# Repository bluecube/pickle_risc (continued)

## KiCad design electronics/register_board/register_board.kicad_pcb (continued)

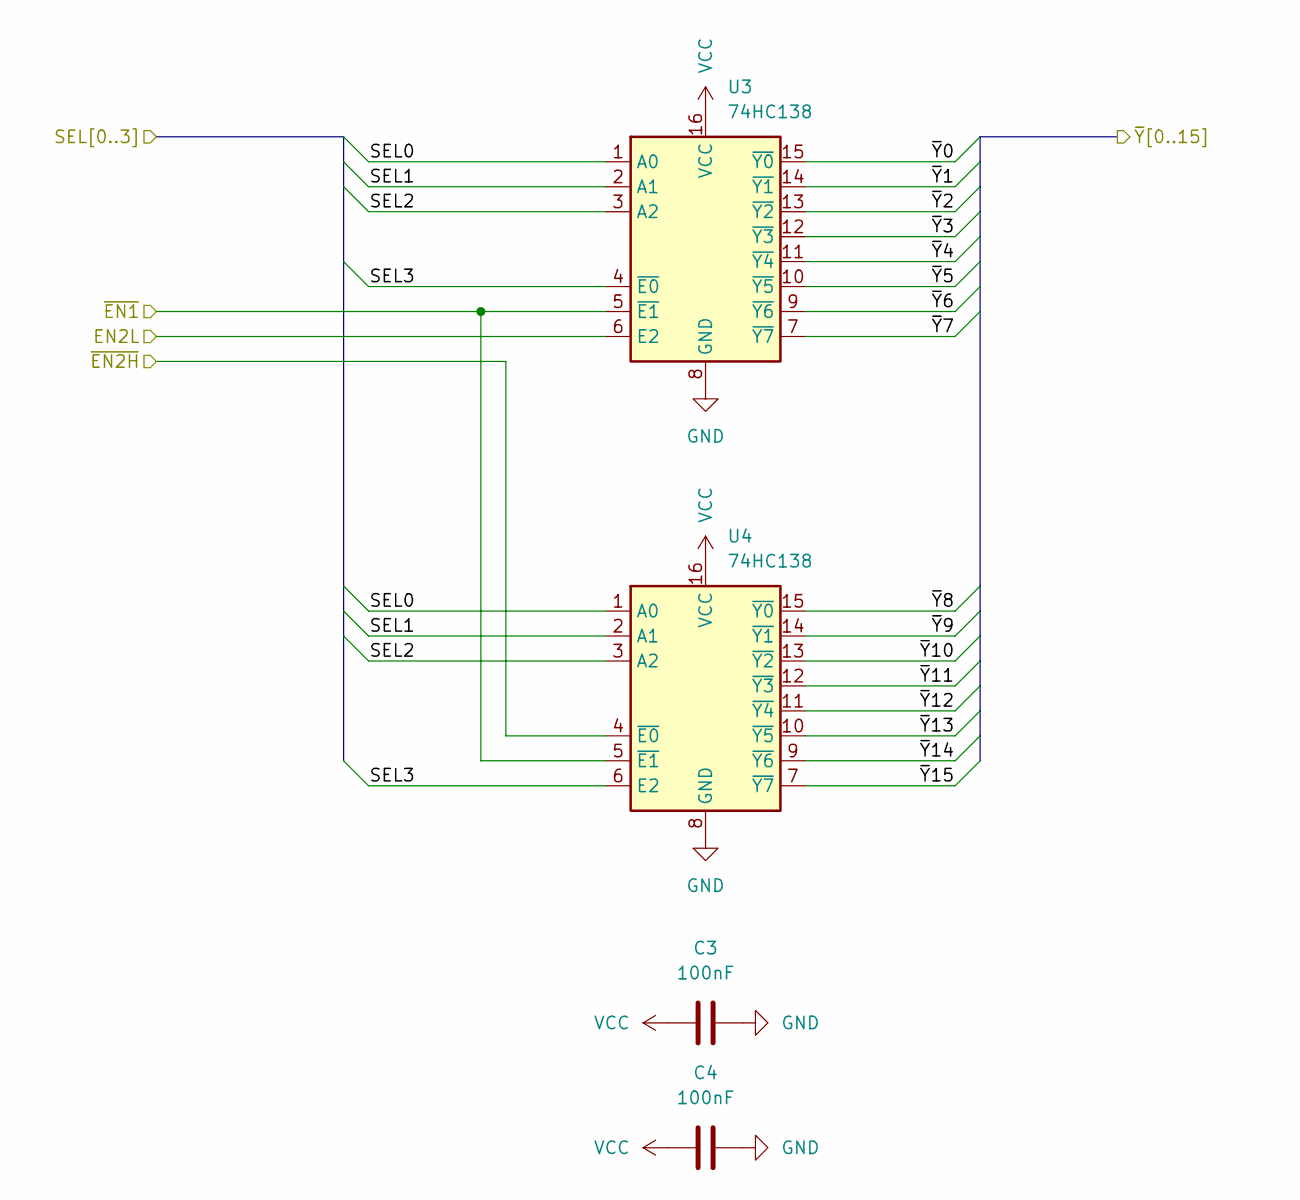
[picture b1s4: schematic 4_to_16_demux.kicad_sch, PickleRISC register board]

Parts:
C3, C4: 100nF; C_0603_1608Metric
U3, U4: 74HC138; TSSOP-16_L5.0-W4.4-P0.65-LS6.4-BL

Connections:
/decoding/4 to 16 demux1/SEL0: U3.1 (A0), U4.1 (A0)
/decoding/4 to 16 demux1/SEL1: U3.2 (A1), U4.2 (A1)
/decoding/4 to 16 demux1/SEL2: U3.3 (A2), U4.3 (A2)
/decoding/4 to 16 demux1/SEL3: U3.4 (~E0), U4.6 (E2)
/decoding/~A_EN: U3.5 (~E1), U4.5 (~E1); also elsewhere on the board
/decoding/~A_EN0: U3.15 (~Y0); also elsewhere on the board
/decoding/~A_EN1: U3.14 (~Y1); also elsewhere on the board
/decoding/~A_EN2: U3.13 (~Y2); also elsewhere on the board
/decoding/~A_EN3: U3.12 (~Y3); also elsewhere on the board
/decoding/~A_EN4: U3.11 (~Y4); also elsewhere on the board
/decoding/~A_EN5: U3.10 (~Y5); also elsewhere on the board
/decoding/~A_EN6: U3.9 (~Y6); also elsewhere on the board
/decoding/~A_EN7: U3.7 (~Y7); also elsewhere on the board
/decoding/~A_EN8: U4.15 (~Y0); also elsewhere on the board
/decoding/~A_EN9: U4.14 (~Y1); also elsewhere on the board
/decoding/~A_EN10: U4.13 (~Y2); also elsewhere on the board
/decoding/~A_EN11: U4.12 (~Y3); also elsewhere on the board
/decoding/~A_EN12: U4.11 (~Y4); also elsewhere on the board
/decoding/~A_EN13: U4.10 (~Y5); also elsewhere on the board
/decoding/~A_EN14: U4.9 (~Y6); also elsewhere on the board
/decoding/~A_EN15: U4.7 (~Y7); also elsewhere on the board
GND: C3.2, C4.2, U3.8 (GND), U4.4 (~E0), U4.8 (GND); also elsewhere on the board
VCC: C3.1, C4.1, U3.6 (E2), U3.16 (VCC), U4.16 (VCC); also elsewhere on the board

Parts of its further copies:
C5, C6, C7, C8: 100nF; C_0603_1608Metric
U5, U6, U7, U8: 74HC138; TSSOP-16_L5.0-W4.4-P0.65-LS6.4-BL

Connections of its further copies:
/B_SEL0: U5.1 (A0), U6.1 (A0)
/B_SEL1: U5.2 (A1), U6.2 (A1)
/B_SEL2: U5.3 (A2), U6.3 (A2)
/B_SEL3: U5.4 (~E0), U6.6 (E2)
/CLK: U7.5 (~E1), U8.5 (~E1); also elsewhere on the board
/D_SEL_LATCHED0: U7.1 (A0), U8.1 (A0); also elsewhere on the board
/D_SEL_LATCHED1: U7.2 (A1), U8.2 (A1); also elsewhere on the board
/D_SEL_LATCHED2: U7.3 (A2), U8.3 (A2); also elsewhere on the board
/D_SEL_LATCHED3: U7.4 (~E0), U8.6 (E2); also elsewhere on the board
/LOAD_LATCHED: U7.6 (E2); also elsewhere on the board
/decoding/4 to 16 demux3/~EN2H: U8.4 (~E0); also elsewhere on the board
/decoding/CLK0: U7.15 (~Y0)
/decoding/CLK1: U7.14 (~Y1); also elsewhere on the board
/decoding/CLK2: U7.13 (~Y2); also elsewhere on the board
/decoding/CLK3: U7.12 (~Y3); also elsewhere on the board
/decoding/CLK4: U7.11 (~Y4); also elsewhere on the board
/decoding/CLK5: U7.10 (~Y5); also elsewhere on the board
/decoding/CLK6: U7.9 (~Y6); also elsewhere on the board
/decoding/CLK7: U7.7 (~Y7); also elsewhere on the board
/decoding/CLK8: U8.15 (~Y0); also elsewhere on the board
/decoding/CLK9: U8.14 (~Y1); also elsewhere on the board
/decoding/CLK10: U8.13 (~Y2); also elsewhere on the board
/decoding/CLK11: U8.12 (~Y3); also elsewhere on the board
/decoding/CLK12: U8.11 (~Y4); also elsewhere on the board
/decoding/CLK13: U8.10 (~Y5); also elsewhere on the board
/decoding/CLK14: U8.9 (~Y6); also elsewhere on the board
/decoding/CLK15: U8.7 (~Y7); also elsewhere on the board
/decoding/~B_EN0: U5.15 (~Y0); also elsewhere on the board
/decoding/~B_EN1: U5.14 (~Y1); also elsewhere on the board
/decoding/~B_EN2: U5.13 (~Y2); also elsewhere on the board
/decoding/~B_EN3: U5.12 (~Y3); also elsewhere on the board
/decoding/~B_EN4: U5.11 (~Y4); also elsewhere on the board
/decoding/~B_EN5: U5.10 (~Y5); also elsewhere on the board
/decoding/~B_EN6: U5.9 (~Y6); also elsewhere on the board
/decoding/~B_EN7: U5.7 (~Y7); also elsewhere on the board
/decoding/~B_EN8: U6.15 (~Y0); also elsewhere on the board
/decoding/~B_EN9: U6.14 (~Y1); also elsewhere on the board
/decoding/~B_EN10: U6.13 (~Y2); also elsewhere on the board
/decoding/~B_EN11: U6.12 (~Y3); also elsewhere on the board
/decoding/~B_EN12: U6.11 (~Y4); also elsewhere on the board
/decoding/~B_EN13: U6.10 (~Y5); also elsewhere on the board
/decoding/~B_EN14: U6.9 (~Y6); also elsewhere on the board
/decoding/~B_EN15: U6.7 (~Y7); also elsewhere on the board
/~B_EN: U5.5 (~E1), U6.5 (~E1)
GND: C5.2, C6.2, C7.2, C8.2, U5.8 (GND), U6.4 (~E0), U6.8 (GND), U7.8 (GND), U8.8 (GND); also elsewhere on the board
VCC: C5.1, C6.1, C7.1, C8.1, U5.6 (E2), U5.16 (VCC), U6.16 (VCC), U7.16 (VCC), U8.16 (VCC); also elsewhere on the board

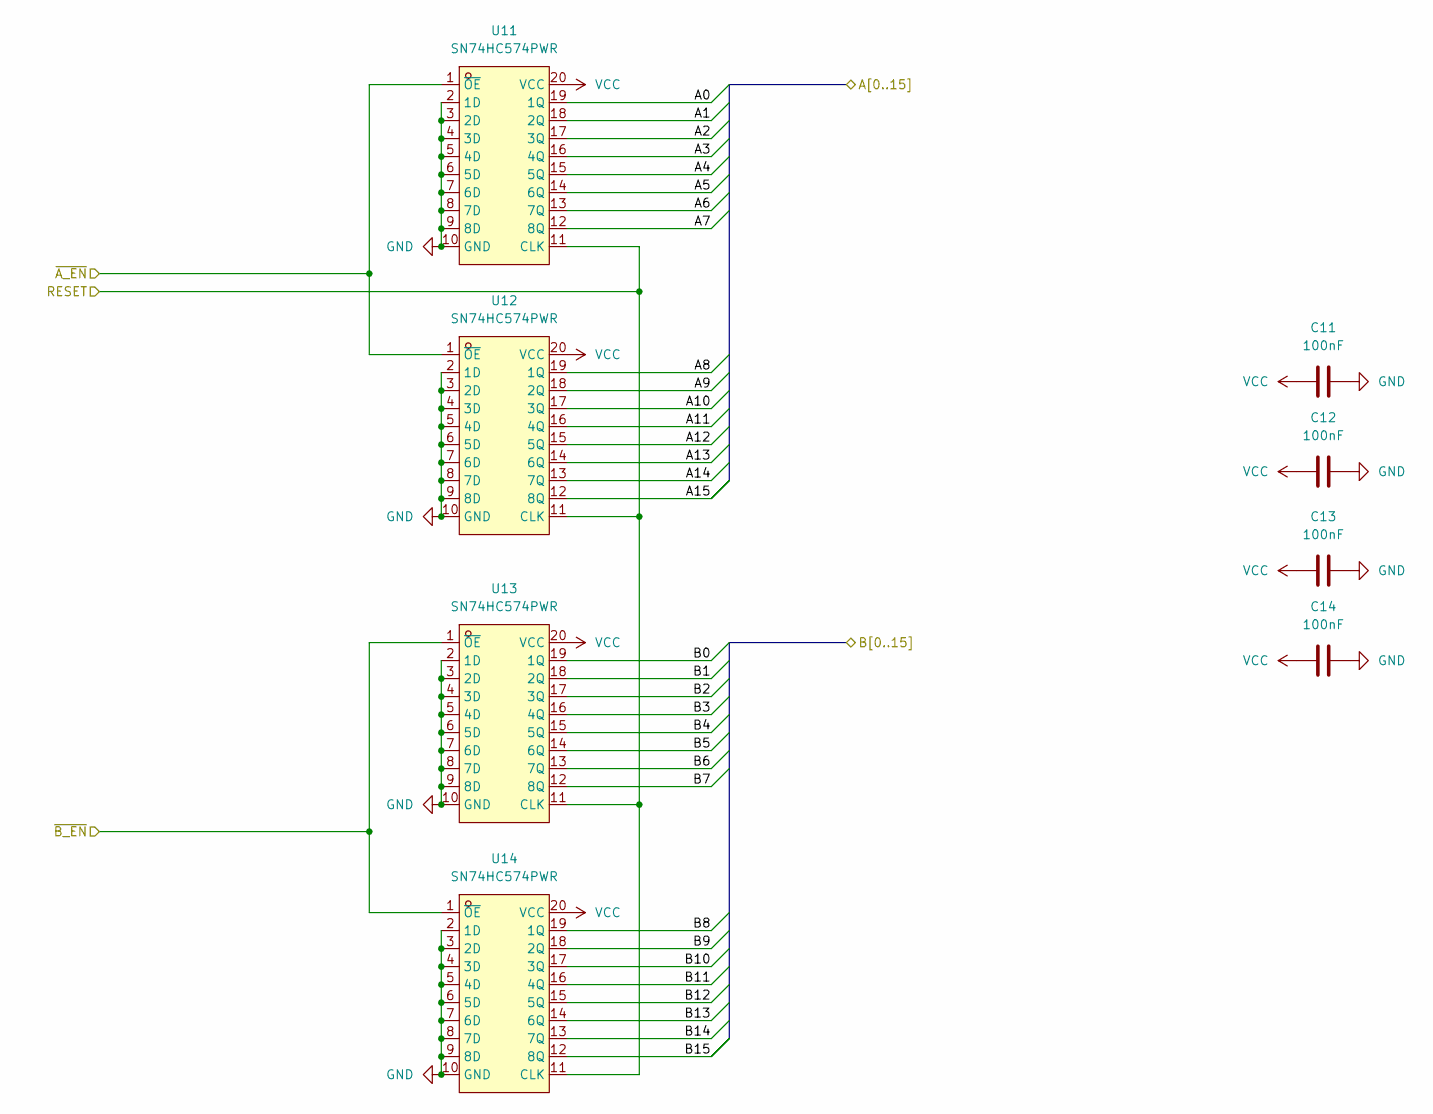
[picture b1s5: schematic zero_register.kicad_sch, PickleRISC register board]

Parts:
C11, C12, C13, C14: 100nF; C_0603_1608Metric
U11, U12, U13, U14: SN74HC574PWR; TSSOP-20_L6.5-W4.4-P0.65-LS6.4-BL; LCSC Part C132111

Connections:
/A0: U11.19 (1Q); also elsewhere on the board
/A1: U11.18 (2Q); also elsewhere on the board
/A2: U11.17 (3Q); also elsewhere on the board
/A3: U11.16 (4Q); also elsewhere on the board
/A4: U11.15 (5Q); also elsewhere on the board
/A5: U11.14 (6Q); also elsewhere on the board
/A6: U11.13 (7Q); also elsewhere on the board
/A7: U11.12 (8Q); also elsewhere on the board
/A8: U12.19 (1Q); also elsewhere on the board
/A9: U12.18 (2Q); also elsewhere on the board
/A10: U12.17 (3Q); also elsewhere on the board
/A11: U12.16 (4Q); also elsewhere on the board
/A12: U12.15 (5Q); also elsewhere on the board
/A13: U12.14 (6Q); also elsewhere on the board
/A14: U12.13 (7Q); also elsewhere on the board
/A15: U12.12 (8Q); also elsewhere on the board
/B0: U13.19 (1Q); also elsewhere on the board
/B1: U13.18 (2Q); also elsewhere on the board
/B2: U13.17 (3Q); also elsewhere on the board
/B3: U13.16 (4Q); also elsewhere on the board
/B4: U13.15 (5Q); also elsewhere on the board
/B5: U13.14 (6Q); also elsewhere on the board
/B6: U13.13 (7Q); also elsewhere on the board
/B7: U13.12 (8Q); also elsewhere on the board
/B8: U14.19 (1Q); also elsewhere on the board
/B9: U14.18 (2Q); also elsewhere on the board
/B10: U14.17 (3Q); also elsewhere on the board
/B11: U14.16 (4Q); also elsewhere on the board
/B12: U14.15 (5Q); also elsewhere on the board
/B13: U14.14 (6Q); also elsewhere on the board
/B14: U14.13 (7Q); also elsewhere on the board
/B15: U14.12 (8Q); also elsewhere on the board
/RESET: U11.11 (CLK), U12.11 (CLK), U13.11 (CLK), U14.11 (CLK)
/decoding/~A_EN0: U11.1 (~OE), U12.1 (~OE); also elsewhere on the board
/decoding/~B_EN0: U13.1 (~OE), U14.1 (~OE); also elsewhere on the board
GND: C11.2, C12.2, C13.2, C14.2, U11.2 (1D), U11.3 (2D), U11.4 (3D), U11.5 (4D), U11.6 (5D), U11.7 (6D), U11.8 (7D), U11.9 (8D), U11.10 (GND), U12.2 (1D), U12.3 (2D), U12.4 (3D), U12.5 (4D), U12.6 (5D), U12.7 (6D), U12.8 (7D), U12.9 (8D), U12.10 (GND), U13.2 (1D), U13.3 (2D), U13.4 (3D), U13.5 (4D), U13.6 (5D), U13.7 (6D), U13.8 (7D), U13.9 (8D), U13.10 (GND), U14.2 (1D), U14.3 (2D), U14.4 (3D), U14.5 (4D), U14.6 (5D), U14.7 (6D), U14.8 (7D), U14.9 (8D), U14.10 (GND); also elsewhere on the board
VCC: C11.1, C12.1, C13.1, C14.1, U11.20 (VCC), U12.20 (VCC), U13.20 (VCC), U14.20 (VCC); also elsewhere on the board

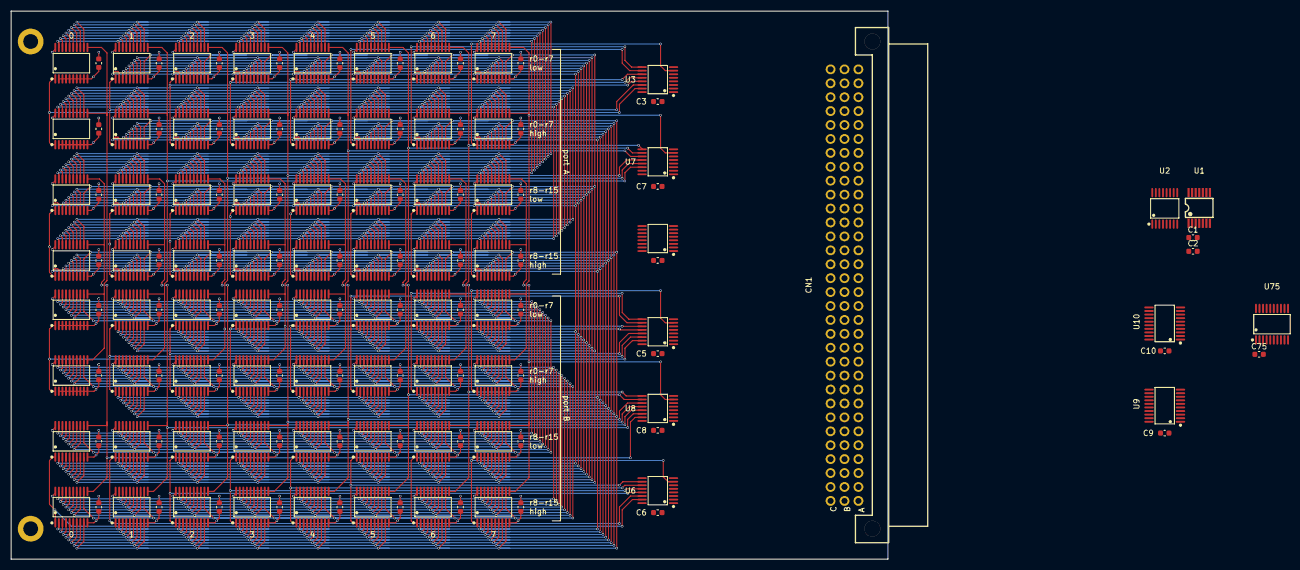
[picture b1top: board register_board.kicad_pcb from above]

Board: 4 copper layers, 160.0 x 100.0 mm, 151 parts (0 on the bottom side), 118 nets.

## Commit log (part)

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2018-11-10 Initial ISA design
2018-11-12 Small isa tweaks
2018-11-12 Moving stuff around.
2019-02-21 Fiddling with ISA
2019-02-21 Added .gitignore
2019-02-21 Started with assembler
2019-04-18 ISA WIP:
    - Specified realistic MMU
    - Half done interrupt spec
    - Settled on using microcode, added multi tick instructions
2019-04-19 Started working on the architecture diagram, More ISA tweaks.
2019-06-18 First design of ALU
2019-06-28 Started simplifying the hardware design to make it workable with 74000 logic
2019-07-01 Working on microcode
2021-12-13 old WIP work (?)
2021-12-15 Simplified addressing registers
2021-12-16 Thinking about MMU
2021-12-16 Removing old design stuff
2022-05-06 Removed beginnings of the old impl
2022-05-06 Starting new architecture
2022-05-07 Cleaned up memory model section
2022-05-07 We want storage!
2022-05-12 Workable but complex instruction set, WIP architecture diagram
2022-05-12 Renamed a file
2022-05-13 Cleaned up the Links section
2022-05-19 More design, this time the instruction set feels more functional
2022-05-19 Renaming a file
2022-05-19 Removed old experiment
2022-05-20 Slightly updated block diagram
2022-05-20 Added Readme
2022-05-20 Thinking about contol lines
2022-05-20 Simpler and more powerful syscall instruction
2022-05-20 Relative jumps need to use signed offsets
2022-05-20 Added opcode map table
2022-05-20 Reorganizing jump instructions
2022-05-20 Reordering instruction fields a bit to simplify the hardware
2022-05-20 More notes
2022-05-21 Big endian
2022-05-21 Synchronizing block diagram with the design, more details
2022-05-21 Updating block diagram
2022-05-21 More compact block diagram
2022-05-27 Register timing notes
2022-05-27 Playing with instruction set
2022-05-29 Fixed arrows in block diagram
2022-05-29 Clarifying complex instructions
2022-06-02 Updated gitignore
2022-06-02 Fixed assignment of cpu control lines to match the block diagram
2022-06-02 Syntactic fixes in instrucion set definitition file
2022-06-03 Easier to parse format of instruction set definition
2022-06-04 Fixed title for break command
2022-06-06 Small fixes
2022-06-06 Skeleton of assembler implementation
2022-06-06 assember: Fixed behavior with invalid characters.
2022-06-06 Add requirements.txt for json5 parsing
2022-06-06 assembler: add header to error messages
2022-06-06 assembler: Add a preparation step before every pass
2022-06-06 assembler: Parsing numeric literals, primitive version of immediate values
2022-06-07 assembler: Detecting overflow in numeric literals
2022-06-07 assembler: Using a typedef for internal numeric types
2022-06-07 assembler: Updated test file with new features
2022-06-07 assembler: Allow underscores in numeric literals
    Same as in python, these are just ignored
2022-06-07 assembler: Refactored tokenizing identifiers into a function
2022-06-07 assembler: Don't allow identifiers starting with question mark
2022-06-07 assembler: Added type-generic stack utility
2022-06-07 assembler: Fix handling of `0`
2022-06-08 assembler: Split main and assembler header
2022-06-10 assembler: Ignoring compile_commands.json
2022-06-10 assembler: Expression parsing
    finished the remaining necessary tokens in tokenizer
2022-06-11 assembler: Fixed assignment instead of comparison
2022-06-12 assembler: Properly working assembler passes and symbol references
    Includes forward references
2022-06-12 assembler: Fail expression parsing when encountering invalid references
2022-06-12 assembler: Support `.db` pseudo-instruction
2022-06-12 assembler: String literals in tokenizer and `.db`
2022-06-12 assembler: `.dw` and `.dd` pseudo-instructions
2022-06-12 assembler: Recursive `.include` directive
2022-06-13 assembler: Sections
2022-06-15 assembler: Output to Intel Hex format
2022-06-15 assembler: Makefile tweaks
2022-06-16 assembler: Minor formating change
2022-06-16 assembler: Verbose printing of assembled instructions
2022-06-17 Generating instruction set documentation from the json5 definition
2022-06-23 assembler: Reworked tokenizer to use peek instead of unget
2022-06-28 Notes about a future filesystem implementation
2022-06-28 Added boot area to FS notes
2022-07-02 Ignore clangd caches
2022-07-05 assembler: Refactored Intel Hex functionality from the assembler output adapter
2022-07-05 assembler: Refactored tokenizer -- separated reading file while keeping location
2022-07-05 assembler: Stack of char is now defined centrally
2022-07-14 WIP emulator
2022-07-14 Added random notes, thinking too far ahead :)
2022-07-15 emulator: More WIP
2022-07-22 Started working on microcode
2022-08-04 A little more work on microcode
2022-08-10 A script to optimize field allocations for the new instruction set. Extremely slow.
2022-08-10 Updating gitignore
2022-08-10 Faster and parallel optimization of the new instruction set field layout
2022-08-15 Explicit use of bitsets in new_instruction_set.py
2022-08-20 Merged logical instruction pairs in the instruction set.
2022-08-21 16reg v2
2022-08-21 New version of instruction assignments
2022-08-21 Don't waste time no zero-sized instructions
2022-09-13 Playing with ideas for simpler single operand design with registers in SRAM
2022-09-20 Fixed instruction encoding assignment overlap with extra opcode bits
2022-09-29 Playing with the instruction set a bit more
2022-10-03 More instruction set stuff
2022-10-05 Cleaning up the repository
2022-10-05 Added notes about graphics
2022-10-05 Finalizing the instruction set rework
2022-10-05 More documentation
2022-10-05 Fixed broken markdown links
2022-10-05 Got rid of substitutions in instruction set json
2022-10-06 Renaming branch instructions to be more C friendly
2022-10-06 assembler: Minor (mostly whitespace) tweaks
2022-10-06 emulator: instruction processing WIP
2022-10-06 We don't need explicit source of zeros in the HW
    zero register is already there
2022-10-11 Updating notes about graphics server
2022-10-11 Top level makefile
2022-10-11 Added byteswap instruction
2022-10-13 emulator: Started working on the rust emulator
    code generation in roughly similar shape as the C/python versio
2022-10-13 emulator: More microcode codegen WIP
2022-10-15 emulator: Quiet down warnings from the generated code
2022-10-15 emulator: Reading and writing virtual memory
2022-10-15 emulator: Refactored instruction set definition loading to a separate crate
2022-10-16 emulator: Tests for sign extending
2022-10-16 emulator: Refactored code for processing fields, moved to util module
2022-10-19 emulator: Hopefully finalized the CPU types
2022-10-19 emulator: Tests for cpu types
2022-10-19 emulator: Two more unit tests
2022-10-19 emulator: Instruction set follows the definition order in Json file
2022-10-19 emulator: substituting blocks of microcode
2022-10-20 emulator: Emulator errors instead of panics
2022-10-23 emulator: Initial implementation of RAM and ROM loaded from intel hex file
2022-10-24 Fixed link
2022-10-26 emulator: Basics of whole system emulation, more work on memory
2022-10-26 emulator: Both library and binary
2022-10-26 emulator: Run rustfmt
2022-10-26 emulator: Disallow starting offset of ROM image
2022-10-26 emulator: Silence some warnings
2022-10-27 Step function for the emulator
2022-10-27 emulator: WIP main.rs
2022-10-28 emulator: Added forgotten dependency
2022-10-28 emulator: Very minimal emulator main loop, crashes immediately
2022-10-28 emulator: Better printing of CPU state
2022-10-28 Reorganizing the rust toolchain
2022-10-30 gitignore and backup exclude is shared for the whole toolchain
2022-10-31 Added a disasselmbler crate to the toolchain
2022-11-01 disassembler: Clippy + rustfmt
2022-11-02 toolchain: Merged disassembler and emulator
    The whole toolchain will now be a single package with multiple binaries
2022-11-02 toolchain: rustfmt
2022-11-02 emulator: Separate microinstruction step
2022-11-02 emulator: Showing disassembly during emulation
2022-11-02 emulator: Fixed memory mapping
2022-11-02 microcode: Fixed loading next instruction
2022-11-02 instruction_set: Fixed most `*i` instructions not using the immediate value.
2022-11-02 emulator: Fixed printing of CPU state
2022-11-02 toolchain: clippy and rustfmt
2022-11-02 emulator: Removing unused code
2022-11-02 emulator: Randomizing system state on init
2022-11-03 toolchain: Reworked matching error state in tests for image
2022-11-03 toolchain: Couple tests for instruction structure
2022-11-03 toolchain: rustfmt and clippy
2022-11-03 toolchain: Reorganizing the source code to make room for assembler
2022-11-05 assembler: Starting with a lexical analyzer
2022-11-05 toolchain: Test for bit field manipulaiton utilities
2022-11-24 assembler: Lexer EOL changes
    - Separated semicolon and EOL tokens
    - Fixed comment not counting as EOL
2022-11-25 WIP parser
2022-11-28 More parsing WIP
2022-11-29 Value parsing tests
2022-11-29 Assignments in assembler
2022-12-02 assembler: WIP
2022-12-04 assembler: Fixed expression parsing bug
    + a few warnings
2022-12-04 assembler: More expression tests, fixing bugs, rustfmt
2022-12-04 assembler: Converting tests to use test_case
2022-12-05 assembler: Separated expression parsing to a new file
2022-12-05 assembler: Filling up the gaps in expression parsing tests
2022-12-11 assembler: Renamed parse state to assembler state
2022-12-11 toolchaing: Renaming testing functions
2022-12-11 assembler: cargo fmt
2022-12-11 assembler: First parser test
2022-12-22 More conversions and testing for instruction stuff.
2022-12-22 Converting instructions to u16, Arbitrary impl, test
2023-01-03 Updated block diagram
2023-01-16 assembler: Major changes in ASM parser
    - Lexer owns data, rather than borrowing.
    - Changed parser from iterator to slice
    - Refactored assembler state to mod.rs
    - Files DB, compatible with codespan_reporting
2023-04-14 Readme update
2023-04-15 instruction set: Less verbose titles
2023-04-16 toolchain: Ported the HTML generator to rust
2023-04-16 New script to rebuild the instruction set HTML overview
2023-04-16 cargo fmt
2023-04-16 assembler: Getting codespan reporting to work, a bit
2023-05-19 Changed to 2 operand 15 register arch
2023-05-23 instruction_set.html: Merged bit groups in overview
2023-05-23 instruction_set: Fixes
2023-05-23 Updating the docs
2023-05-24 instruction set: Fixes
2023-05-24 instruction set: Added memory instructions with address post-increment
2023-07-29 Added lisp note
2023-07-29 Updated generated instruction set overview
2025-09-16 A new fancy 3 operand instruction set
2025-09-16 Temporarily ignore electornics from git
2025-09-17 Cutting down the toolchain, start working on the new iteration
2025-09-17 Updating GPU notes
2025-09-19 Moved Lisp notes from main branch
2025-09-19 Simplifying instruction set to work with pipelined design
2025-09-23 Cleaned up and updated Cargo.toml
2025-09-23 First attempts at writing assembly for the platform
    WIP and not tested at alll
2025-09-23 More work on the architecture
2025-10-03 Working on the assembler
2025-10-08 Some more notes
2025-12-28 Updated block diagram and instruction set
2025-12-28 WIP register board in EasyEDA
    This is going to go away soon
2025-12-28 WIP Register board
    Schematic is probably finished, PCB is 75%.
2025-12-29 SystemVerilog model for register board + python tests
2026-01-04 Gitignore updates
2026-01-04 Tweaking the block diagram
    Now includes the split between physical boards
2026-01-06 Complex property based test for register board
2026-01-06 More tweaking of block diagram
2026-01-12 Clarifying architecture details around the ALU board
2026-01-12 Got rid of LL/SC
    Disabling interrupts in kernel mode will be enough.
2026-01-12 Small tweaks
2026-01-13 More smalltweaks
2026-01-28 Updating design
2026-01-28 Updated WIP register board PCB
2026-02-02 Updating graphics note
2026-02-03 Thinking through interrupts some more
2026-03-21 Couple more notes
2026-03-21 Replaced space with underscore in block diagram filename
